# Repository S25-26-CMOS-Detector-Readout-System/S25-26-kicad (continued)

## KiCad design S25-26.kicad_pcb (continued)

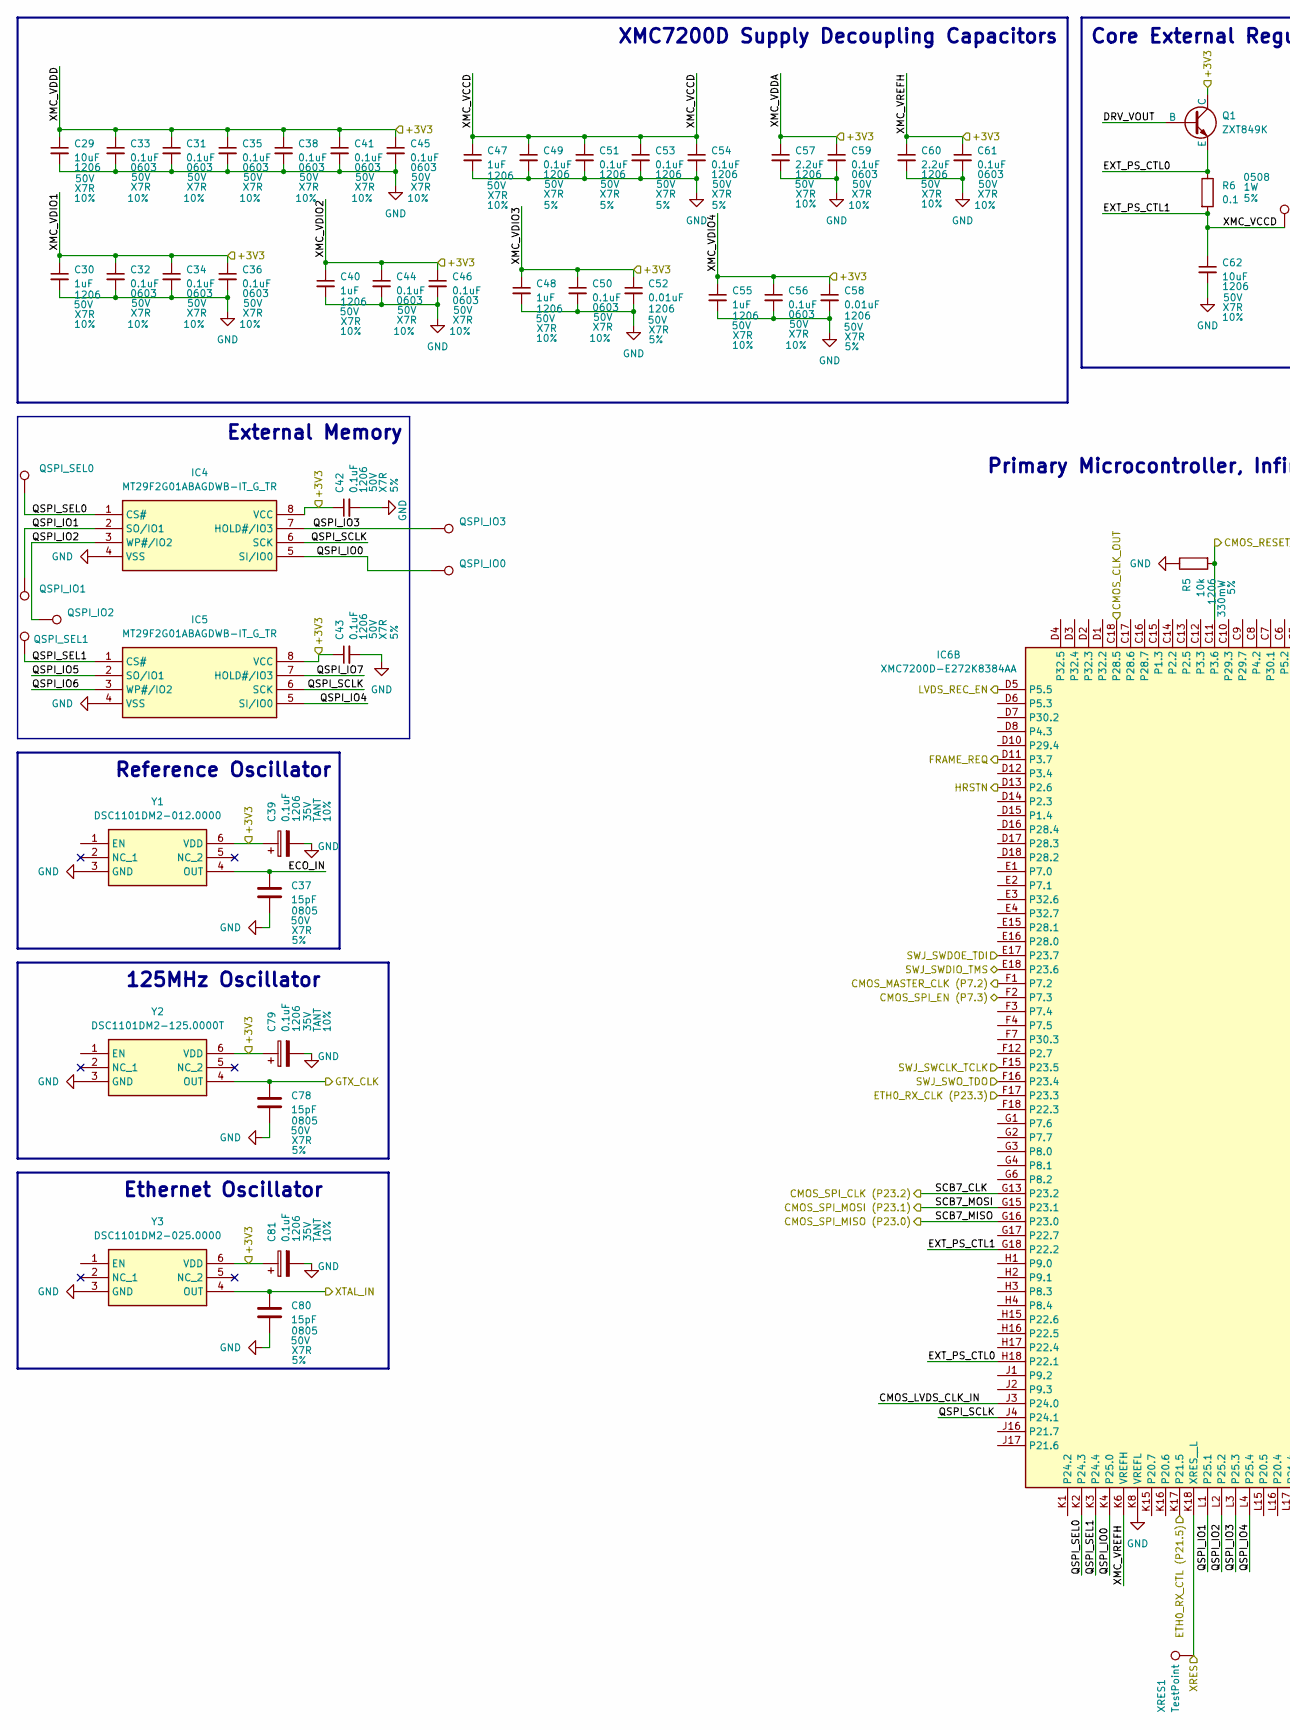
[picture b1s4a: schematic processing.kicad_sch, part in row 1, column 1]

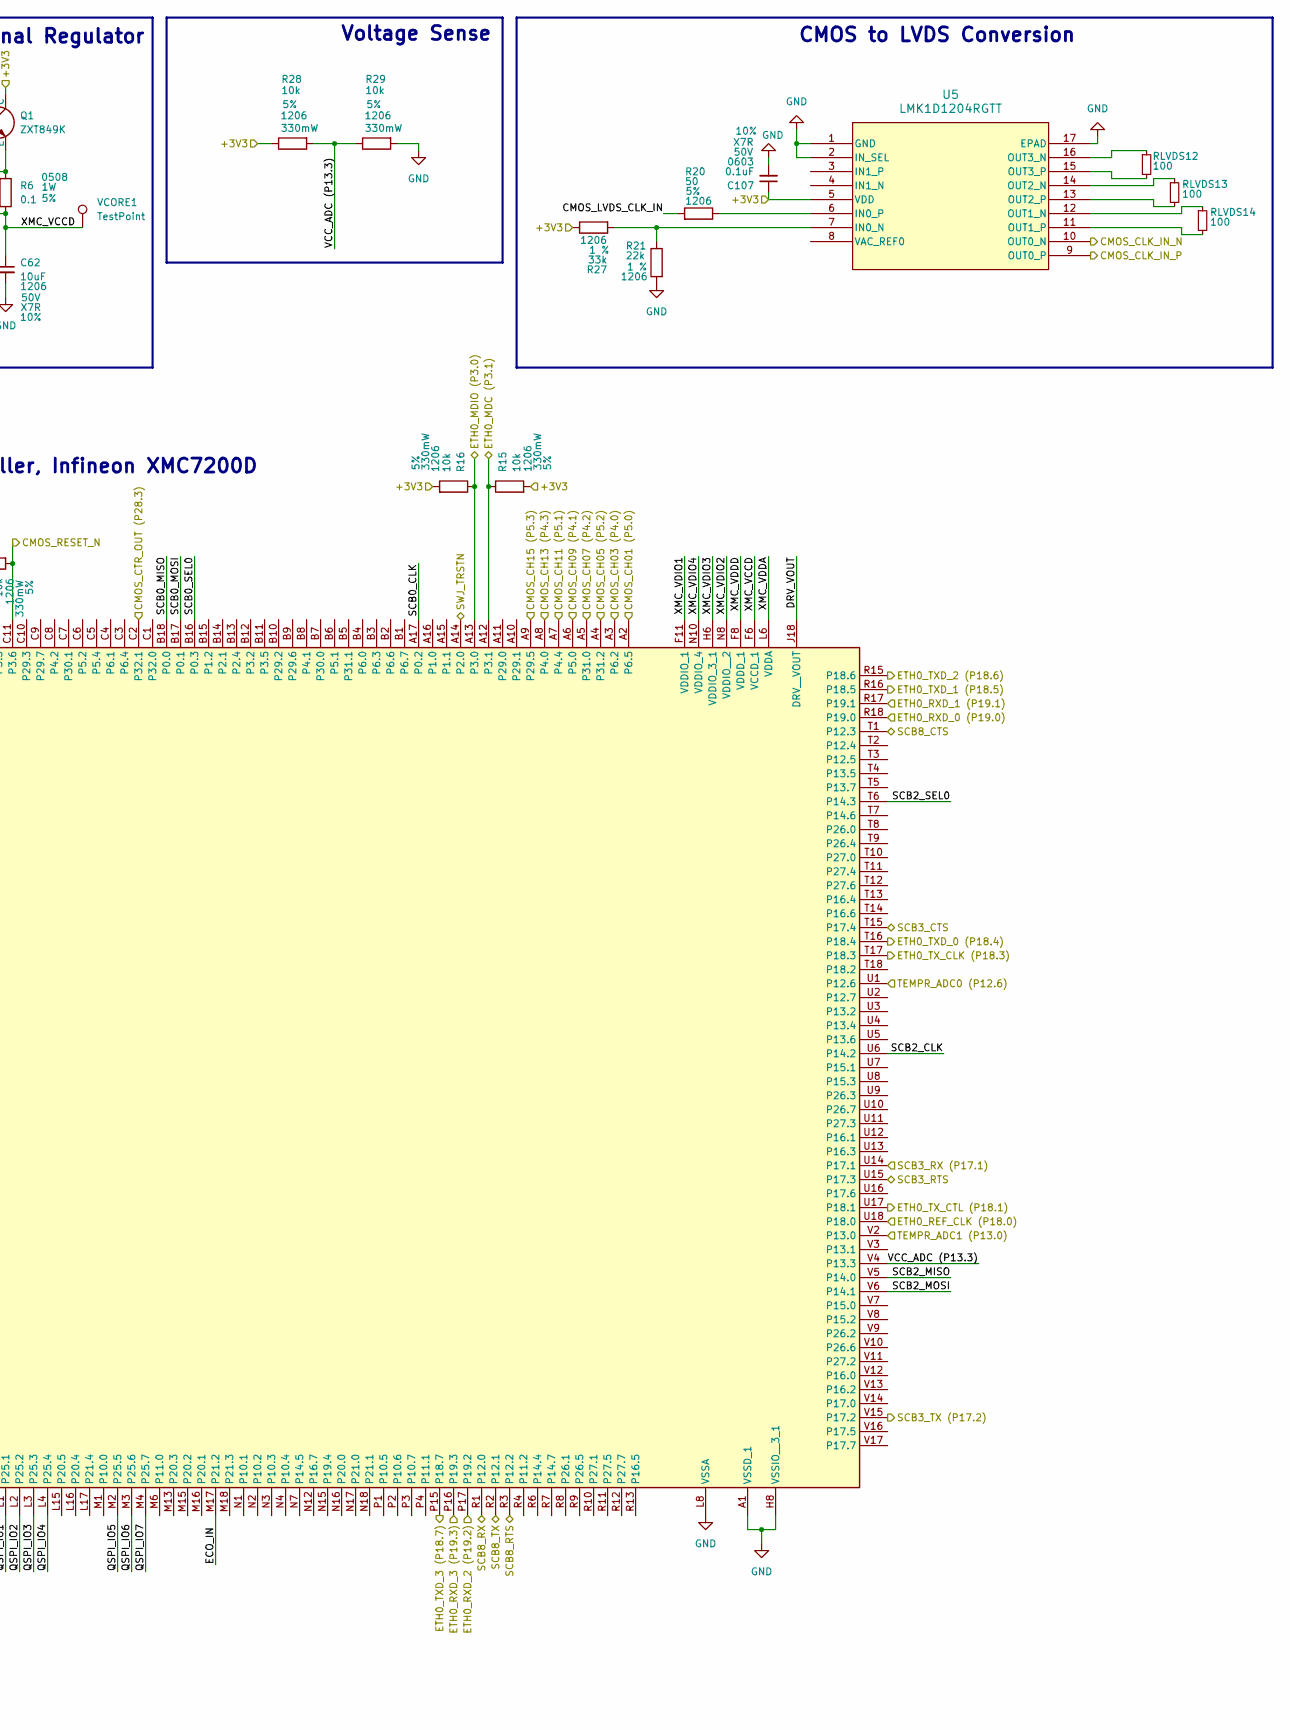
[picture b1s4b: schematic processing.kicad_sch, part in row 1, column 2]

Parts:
C29, C62: 10uF; C_1206_3216Metric; Voltage Rating 50V; Tolerance 10%; Mouser Part Number 187-CL31B106KBK6PJE
C30, C40, C47, C48, C55: 1uF; C_1206_3216Metric; Voltage Rating 50V; Tolerance 10%; Mouser Part Number 963-UMK316B7105KL-T
C31, C32, C33, C34, C35, C36, C38, C41, C44, C45, C46, C50, C56, C59, C61, C107: 0.1uF; C_0603_1608Metric; Voltage Rating 50V; Tolerance 10%; Mouser Part Number 963-UMK107B7104KAHT
C37, C78, C80: 15pF; C_0805_2012Metric; Voltage Rating 50V; Tolerance 5%; Mouser Part Number 80-C0805C150J5RACTU
C39, C79, C81: 0.1uF; C_1206_3216Metric; Voltage Rating 35V; Tolerance 10%; Mouser Part Number 581-TAJA104K035SNJ
C42, C43, C49, C51, C53, C54: 0.1uF; C_1206_3216Metric; Voltage Rating 50V; Tolerance 5%; Mouser Part Number 581-12065C104J4Z2A
C52, C58: 0.01uF; C_1206_3216Metric; Voltage Rating 50V; Tolerance 5%; Mouser Part Number 581-12065C103J4T4A
C57, C60: 2.2uF; C_1206_3216Metric; Voltage Rating 50V; Tolerance 10%; Mouser Part Number 80-C1206X225K5REAULR
IC4, IC5: MT29F2G01ABAGDWB-IT_G_TR; SON127P800X600X65-8N; Manufacturer_Part_Number MT29F2G01ABAGDWB-IT:G TR; Mouser Part Number 340-319922-REEL
IC6: XMC7200D-E272K8384AA; BGA272C80P18X18_1600X1600X170; Manufacturer_Part_Number XMC7200D-E272K8384AA; Mouser Part Number 726-C7200DE272K8384A
Q1: ZXT849K; TO-252-3_TabPin4; Mouser Part Number 522-ZXT849KTC
QSPI_IO0: QSPI_IO0; TestPoint_Pad_2.0x2.0mm
QSPI_IO1: QSPI_IO1; TestPoint_Pad_2.0x2.0mm
QSPI_IO2: QSPI_IO2; TestPoint_Pad_2.0x2.0mm
QSPI_IO3: QSPI_IO3; TestPoint_Pad_2.0x2.0mm
QSPI_SEL0: QSPI_SEL0; TestPoint_Pad_2.0x2.0mm
QSPI_SEL1: QSPI_SEL1; TestPoint_Pad_2.0x2.0mm
R5, R15, R16, R28, R29: 10k; R_1206_3216Metric; Power Rating 330mW; Tolerance 5%; Mouser Part Number 667-ERJ-T08J103V
R6: 0.1; R_1206_3216Metric; Power Rating 1W; Tolerance 5%; Mouser Part Number 755-LTR10LEZPJLR10
R20: 50; R_1206_3216Metric; Tolerance 5%
R21: 22k; R_1206_3216Metric; Tolerance 1 %
R27: 33k; R_1206_3216Metric; Tolerance 1 %
RLVDS12, RLVDS13, RLVDS14: 100; R_0603_1608Metric; Power Rating 0.2W; Tolerance 1%; Mouser Part Number 667-ERJ-P03F1000V
U5: LMK1D1204RGTT; VQFN16_RGT_TEX; Digikey Part Number 296-LMK1D1204RGTTCT-ND
VCORE1: TestPoint; TestPoint_Pad_D1.0mm
XRES1: TestPoint; TestPoint_Pad_D1.0mm
Y1: DSC1101DM2-012.0000; DSC1101DM20120000; Manufacturer_Part_Number DSC1101DM2-012.0000; Mouser Part Number 579-DSC1101DM2012
Y2: DSC1101DM2-125.0000T; DSC1101DM20120000; Manufacturer_Part_Number DSC1101DM2-125.0000T; Mouser Part Number 998-1101DM2125.0000T
Y3: DSC1101DM2-025.0000; DSC1101DM20120000; Manufacturer_Part_Number DSC1101DM2-025.0000; Mouser Part Number 998-1101DM2025.0000

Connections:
+3V3: C29.1, C30.1, C31.1, C32.1, C33.1, C34.1, C35.1, C36.1, C38.1, C39.1, C40.1, C41.1, C42.1, C43.1, C44.1, C45.1, C46.1, C48.1, C50.1, C52.1, C55.1, C56.1, C57.1, C58.1, C59.1, C60.1, C61.1, C79.1, C81.1, C107.1, IC4.8 (VCC), IC5.8 (VCC), IC6.F8 (VDDD_1), IC6.F9 (VDDIO__1_1), IC6.F10 (VDDIO__1_2), IC6.F11 (VDDIO_1), IC6.H6 (VDDIO_3_1), IC6.H13 (VDDD_2), IC6.J6 (VDDIO_3_2), IC6.J13 (VDDD_3), IC6.K6 (VREFH), IC6.K13 (VDDD_4), IC6.L6 (VDDA), IC6.L13 (VDDD_5), IC6.N8 (VDDIO__2), IC6.N9 (VDDIO__4), IC6.N10 (VDDIO_4), IC6.N11 (VDDD_6), Q1.1 (C), R15.2, R16.2, R27.1, R28.1, U5.5 (VDD), Y1.6 (VDD), Y2.6 (VDD), Y3.6 (VDD); also elsewhere on the board
/CMOS_CLK_IN_N: U5.10 (OUT0_N); also elsewhere on the board
/CMOS_CLK_IN_P: U5.9 (OUT0_P); also elsewhere on the board
/CMOS_MASTER_CLK: IC6.F1 (P7.2); also elsewhere on the board
/CMOS_RESET_N: IC6.C11 (P3.6), R5.2; also elsewhere on the board
/CMOS_SPI_CLK: IC6.G13 (P23.2); also elsewhere on the board
/CMOS_SPI_EN: IC6.F2 (P7.3); also elsewhere on the board
/CMOS_SPI_MISO: IC6.G16 (P23.0); also elsewhere on the board
/CMOS_SPI_MOSI: IC6.G15 (P23.1); also elsewhere on the board
/ETH0_MDC: IC6.A12 (P3.1), R15.1; also elsewhere on the board
/ETH0_MDIO: IC6.A13 (P3.0), R16.1; also elsewhere on the board
/ETH0_RXD_0: IC6.R18 (P19.0); also elsewhere on the board
/ETH0_RXD_1: IC6.R17 (P19.1); also elsewhere on the board
/ETH0_RXD_2: IC6.P17 (P19.2); also elsewhere on the board
/ETH0_RXD_3: IC6.P16 (P19.3); also elsewhere on the board
/ETH0_RX_CLK: IC6.F17 (P23.3); also elsewhere on the board
/ETH0_RX_CTL: IC6.K17 (P21.5); also elsewhere on the board
/ETH0_TXD_0: IC6.T16 (P18.4); also elsewhere on the board
/ETH0_TXD_1: IC6.R16 (P18.5); also elsewhere on the board
/ETH0_TXD_2: IC6.R15 (P18.6); also elsewhere on the board
/ETH0_TXD_3: IC6.P15 (P18.7); also elsewhere on the board
/ETH0_TX_CLK: IC6.T17 (P18.3); also elsewhere on the board
/ETH0_TX_CTL: IC6.U17 (P18.1); also elsewhere on the board
/FRAME_REQ: IC6.D11 (P3.7); also elsewhere on the board
/LVDS Conversion/CMOS_CH01: IC6.A2 (P6.5); also elsewhere on the board
/LVDS Conversion/CMOS_CH03: IC6.A3 (P6.2); also elsewhere on the board
/LVDS Conversion/CMOS_CH05: IC6.A4 (P31.2); also elsewhere on the board
/LVDS Conversion/CMOS_CH07: IC6.A5 (P31.0); also elsewhere on the board
/LVDS Conversion/CMOS_CH09: IC6.A6 (P5.0); also elsewhere on the board
/LVDS Conversion/CMOS_CH11: IC6.A7 (P4.4); also elsewhere on the board
/LVDS Conversion/CMOS_CH13: IC6.A8 (P4.0); also elsewhere on the board
/LVDS Conversion/CMOS_CH15: IC6.A9 (P29.5); also elsewhere on the board
/LVDS Conversion/CMOS_CLK_OUT: IC6.C18 (P28.5); also elsewhere on the board
/LVDS Conversion/CMOS_CTR_OUT: IC6.C2 (P32.1); also elsewhere on the board
/LVDS Conversion/LVDS_RECV_EN: IC6.D5 (P5.5); also elsewhere on the board
/Processing/CMOS_LVDS_CLK_IN: IC6.J3 (P24.0), R20.2
/Processing/DRV_VOUT: IC6.J18 (DRV__VOUT), Q1.2 (B)
/Processing/ECO_IN: C37.1, IC6.M17 (P21.2), Y1.4 (OUT)
/Processing/ETH0_REF_CLK (P18.0): C78.1, IC6.U18 (P18.0), Y2.4 (OUT); also elsewhere on the board
/Processing/EXT_PS_CTL0: IC6.H18 (P22.1), Q1.3 (E), R6.1
/Processing/EXT_PS_CTL1: C47.1, C49.1, C51.1, C53.1, C54.1, C62.1, IC6.F6 (VCCD_1), IC6.F13 (VCCD_2), IC6.G18 (P22.2), IC6.N6 (VCCD_3), IC6.N13 (VCCD_4), R6.2, VCORE1.1
/Processing/HRSTN: IC6.D13 (P2.6)
/Processing/QSPI_IO0: IC4.5 (SI/IO0), IC6.K4 (P25.0), QSPI_IO0.1
/Processing/QSPI_IO1: IC4.2 (SO/IO1), IC6.L1 (P25.1), QSPI_IO1.1
/Processing/QSPI_IO2: IC4.3 (WP#/IO2), IC6.L2 (P25.2), QSPI_IO2.1
/Processing/QSPI_IO3: IC4.7 (HOLD#/IO3), IC6.L3 (P25.3), QSPI_IO3.1
/Processing/QSPI_IO4: IC5.5 (SI/IO0), IC6.L4 (P25.4)
/Processing/QSPI_IO5: IC5.2 (SO/IO1), IC6.M2 (P25.5)
/Processing/QSPI_IO6: IC5.3 (WP#/IO2), IC6.M3 (P25.6)
/Processing/QSPI_IO7: IC5.7 (HOLD#/IO3), IC6.M4 (P25.7)
/Processing/QSPI_SCLK: IC4.6 (SCK), IC5.6 (SCK), IC6.J4 (P24.1)
/Processing/QSPI_SEL0: IC4.1 (CS#), IC6.K2 (P24.3), QSPI_SEL0.1
/Processing/QSPI_SEL1: IC5.1 (CS#), IC6.K3 (P24.4), QSPI_SEL1.1
/Processing/SCB0_CLK: IC6.A17 (P0.2)
/Processing/SCB0_MISO: IC6.B18 (P0.0)
/Processing/SCB0_MOSI: IC6.B17 (P0.1)
/Processing/SCB0_SEL0: IC6.B16 (P0.3)
/Processing/SCB2_CLK: IC6.U6 (P14.2)
/Processing/SCB2_MISO: IC6.V5 (P14.0)
/Processing/SCB2_MOSI: IC6.V6 (P14.1)
/Processing/SCB2_SEL0: IC6.T6 (P14.3)
/Processing/SCB3_CTS: IC6.T15 (P17.4); also elsewhere on the board
/Processing/SCB3_RTS: IC6.U15 (P17.3); also elsewhere on the board
/Processing/SCB3_RX (P17.1): IC6.U14 (P17.1); also elsewhere on the board
/Processing/SCB3_TX (P17.2): IC6.V15 (P17.2); also elsewhere on the board
/Processing/SCB8_CTS: IC6.T1 (P12.3); also elsewhere on the board
/Processing/SCB8_RTS: IC6.R3 (P12.2); also elsewhere on the board
/Processing/SCB8_RX: IC6.R1 (P12.0); also elsewhere on the board
/Processing/SCB8_TX: IC6.R2 (P12.1); also elsewhere on the board
/Processing/SWJ_SWCLK_TCLK: IC6.F15 (P23.5); also elsewhere on the board
/Processing/SWJ_SWDIO_TMS: IC6.E18 (P23.6); also elsewhere on the board
/Processing/SWJ_SWDOE_TDI: IC6.E17 (P23.7); also elsewhere on the board
/Processing/SWJ_SWO_TDO: IC6.F16 (P23.4); also elsewhere on the board
/Processing/SWJ_TRSTN: IC6.A14 (P2.0)
/Processing/TEMPR_ADC0 (P12.6): IC6.U1 (P12.6); also elsewhere on the board
/Processing/TEMPR_ADC1 (P13.0): IC6.V2 (P13.0); also elsewhere on the board
/Processing/VCC_ADC (P13.3): IC6.V4 (P13.3), R28.2, R29.1
/Processing/XRES: IC6.K18 (XRES__L), XRES1.1; also elsewhere on the board
/Processing/XTAL_IN: C80.1, Y3.4 (OUT); also elsewhere on the board
GND: C29.2, C30.2, C31.2, C32.2, C33.2, C34.2, C35.2, C36.2, C37.2, C38.2, C39.2, C40.2, C41.2, C42.2, C43.2, C44.2, C45.2, C46.2, C47.2, C48.2, C49.2, C50.2, C51.2, C52.2, C53.2, C54.2, C55.2, C56.2, C57.2, C58.2, C59.2, C60.2, C61.2, C62.2, C78.2, C79.2, C80.2, C81.2, C107.2, IC4.4 (VSS), IC5.4 (VSS), IC6.A1 (VSSD_1), IC6.A18 (VSSD_2), IC6.D9 (VSSD_3), IC6.G7 (VSSD_4), IC6.G12 (VSSD_5), IC6.H8 (VSSIO__3_1), IC6.H9 (VSSD_6), IC6.H10 (VSSD_7), IC6.H11 (VSSD_8), IC6.J8 (VSSIO__3_2), IC6.J9 (VSSD_9), IC6.J10 (VSSD_10), IC6.J11 (VSSD_11), IC6.J15 (VSSD_12), IC6.K8 (VREFL), IC6.K9 (VSSD_13), IC6.K10 (VSSD_14), IC6.K11 (VSSD_15), IC6.L8 (VSSA), IC6.L9 (VSSIO__4_1), IC6.L10 (VSSIO__4_2), IC6.L11 (VSSD__1), IC6.L18 (VSSD__2_1), IC6.M7 (VSSD_16), IC6.M12 (VSSD_17), IC6.P18 (VSSD__2_2), IC6.R5 (VSSD_18), IC6.R14 (VSSD_19), IC6.V1 (VSSD_20), IC6.V18 (VSSD_21), R5.1, R21.2, R29.2, U5.1 (GND), U5.2 (IN_SEL), U5.17 (EPAD), Y1.3 (GND), Y2.3 (GND), Y3.3 (GND); also elsewhere on the board
unnamed: R21.1, R27.2, U5.7 (IN0_N)
unnamed: R20.1, U5.6 (IN0_P)
unnamed: RLVDS14.1, U5.12 (OUT1_N)
unnamed: RLVDS14.2, U5.11 (OUT1_P)
unnamed: RLVDS13.1, U5.14 (OUT2_N)
unnamed: RLVDS13.2, U5.13 (OUT2_P)
unnamed: RLVDS12.1, U5.16 (OUT3_N)
unnamed: RLVDS12.2, U5.15 (OUT3_P)

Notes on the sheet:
Voltage Sense
Ethernet Oscillator
125MHz Oscillator
External Memory
Reference Oscillator
XMC7200D Supply Decoupling Capacitors
CMOS to LVDS Conversion
Primary Microcontroller, Infineon XMC7200D
Core External Regulator

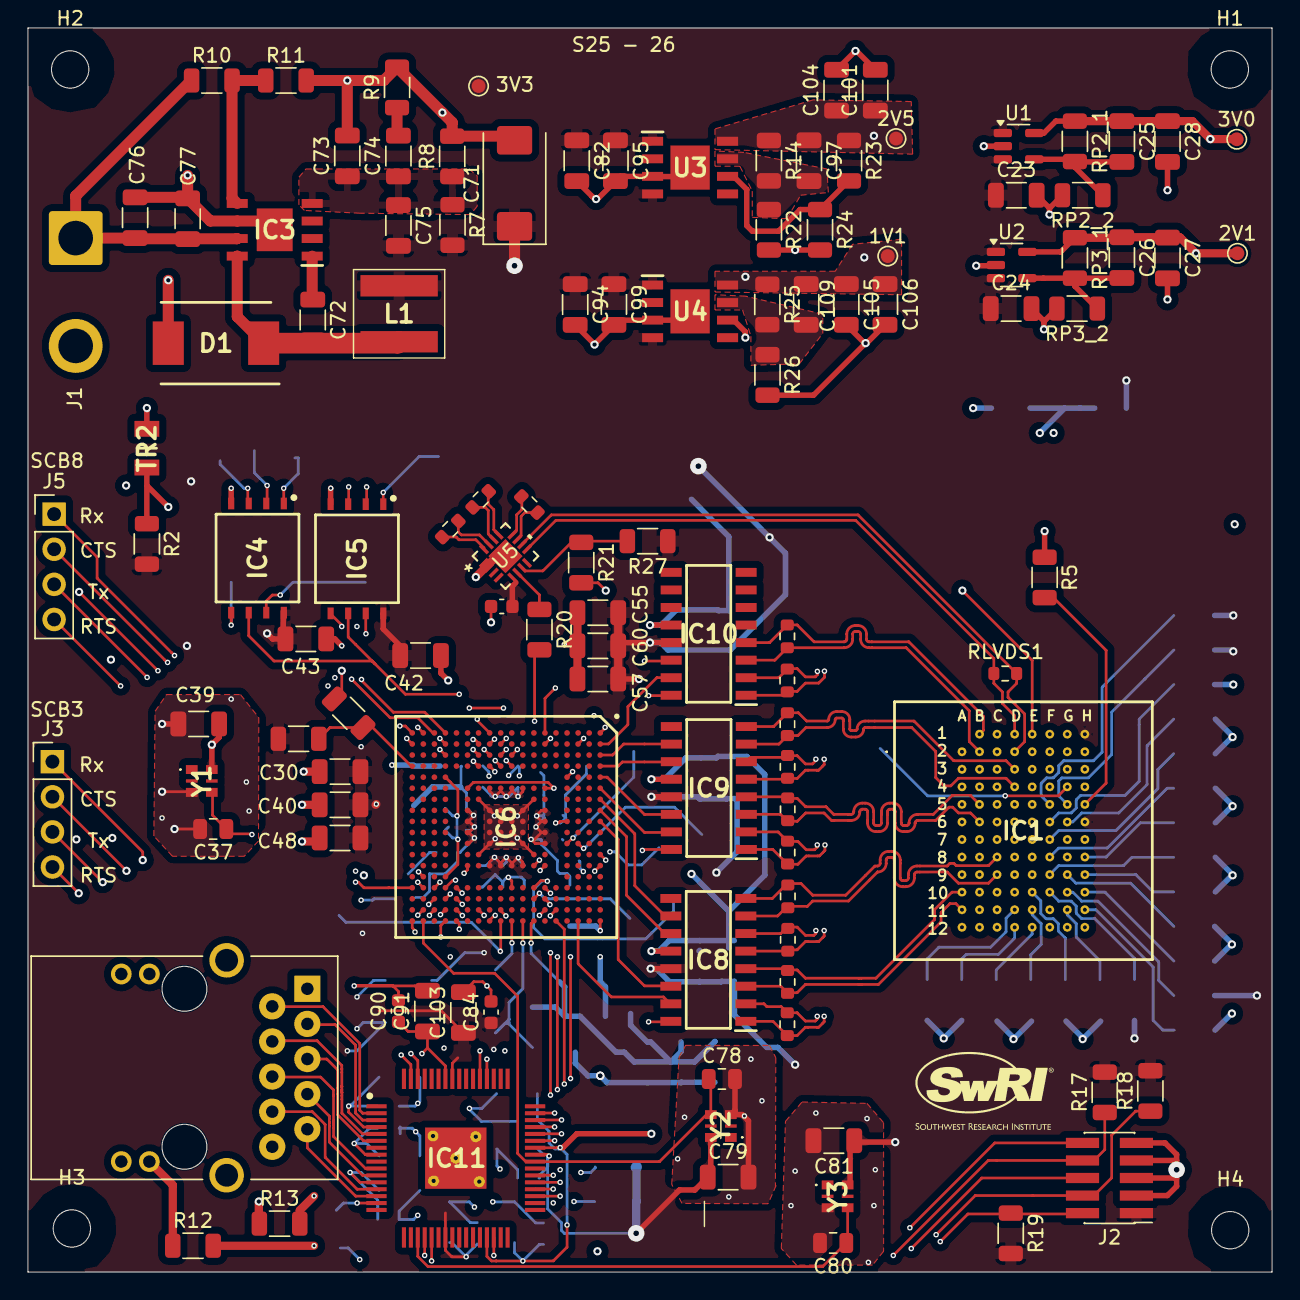
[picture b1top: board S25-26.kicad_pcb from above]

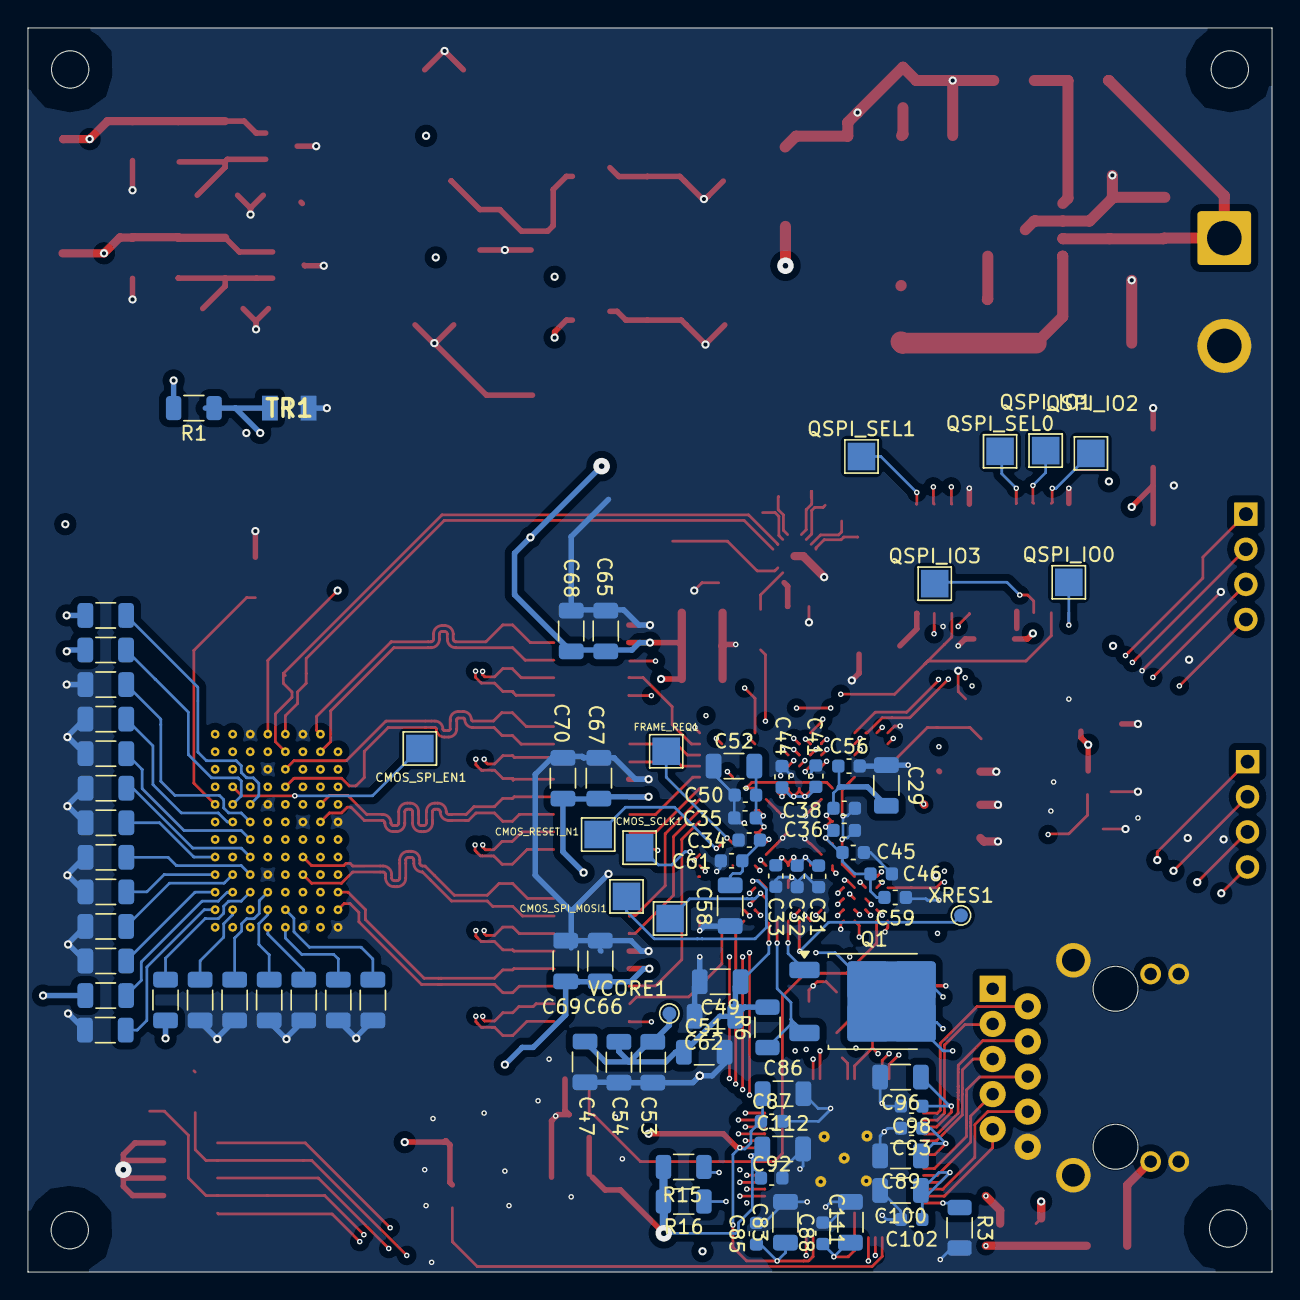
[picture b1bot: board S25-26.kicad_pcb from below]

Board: 6 copper layers, 90.0 x 90.0 mm, 202 parts (85 on the bottom side), 146 nets.

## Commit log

2024-11-13 Imported ICs
    Imported LVDS Receiver and Driver ICS and Voltage Regulator IC.
2024-11-15 First Draft
    Added Power Regulation, LVDS Serialization, and Processing sheets. Created schematics for voltage regulators and LVDS receivers, including inputs and outputs. Added symbols for all components. Added 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
2024-11-18 Ethernet Connections made; SPI connections made; TODO list in processing schem
2024-11-22 Corrected LVDS
2024-11-22 Processing Updates
    Added LVCMOS connections to MCU, added power regulation to MCU (NOT COMPLETE!)
2024-11-23 Added lots more connections
2024-12-03 Some Colors; GND net ties
2024-12-03 Condensed to one page schematic; added decoupling capacitors on MCU; added CLK connections, currently assuming any PWM pins can act as clkout, docs are rather vague; redid LVDS connections to represe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
2024-12-03 Add some preliminary pin connectors and RJ45; fix some ethernet phy connections
2024-12-23 Voltage Regulator Minor Edits
    Changed how the I/Os of the voltage regulation systems look, using the specific input and output labels.
2024-12-23 Voltage Input Symbols Edited
    Changed into global input/output symbols for easier readability
2025-01-24 Implementing Global Labels
    Swapping generic I/O labels for global labels to help provide clarity in the schematic. Completed Supply Decoupling Caps, Temp. Sensing, Voltage Regulation, and part of Core Ext. Regulator
2025-02-05 Reverted schematic to hierarchical structure.
    The following connections are known to be floating:
    FRAME_REQ
    CMOS_RESET_N
    CMOS_CLK_OUT
    ETH0_RX_ER
    ETH0_ETH_TSU_TIMER_CMP_VAL
2025-02-05 Auto Generated PCB
    Autogenerated PCB and found substitute footprint for the linear voltage regulator
2025-02-05 Some small revisions
2025-02-05 One gnd to rule them all; PCB border (90 mm x 90 mm)
2025-02-05 3v3 Regulator routed; zones for 3v3 and gnd
2025-02-07 Schematic - Component Specifics
    Fixed floating connections.
    Added parameters, footprints, Mouser part numbers, and Mouser links to all symbols, including discrete components and ICs.
    The following symbols do not have Mouser part numbers or Mouser links:
    CMOS Sensor (not required)
    RJ45 Connector
    JTAG Connector
2025-02-12 QSPI Lines for 100 MHz channel
2025-02-12 Some small changes for BOM
2025-02-15 Ethernet Transceiver
2025-02-17 Memory layout completed
2025-02-21 Lots of PCB changes, some small parts changes
    Updated parts footprints from those found in MDE Lab. Some parameters may be incorrect, but all footprints should be correct
    Drew most of PCB. CMOS SPI still needs connection. Decoupling caps on MCU still need connection. Power and ground needs to be analyzed, and some components may not have power or ground connected.
2025-02-24 Adjusted board setup for AdvancedPCB; fixed many DRC errors
2025-02-24 Fixed DRC; all connections made
2025-02-26 Testpads everywhere; passives' footprints updated from MDE components; bigger DC_IN pads
2025-02-27 move toplevel to accomadate test pads
2025-02-28 Final Changes before Order
2025-03-05 Watch Out: David's Mounting Holes
2025-03-25 Lots of small changes
    Some power and ground planes need to be looked at
    All parts need to be reexamined before ordering
2025-03-25 See previous push
2025-03-26 Added text to pinheaders for JTAG and UART
2025-03-27 Almost done
    Taking a break and making a push. Known things to do:
    Add pull-up resistors to ETH MDIO, ETH MDC, and XRESL.
    Source a 100uF capacitor for primary regulator.
2025-03-28 Ready to order
    Still unsure about 100uF cap
2025-03-28 Labeled test pads; marked tantalums with lines for cathode; found suitable tantalum for 100 uF
2025-03-28 S25 - 26 Text Added
2025-03-29 Some teeny changes
2025-04-02 CMOS Sensor Grid Text
2025-04-18 Beginning of V3
    Long way to go
2025-04-19 Excluded TPs from BOM
2025-04-22 V3 Overhaul
    Things remaining:
    Ethernet Transceiver Clocks
    Output Filtering on DC-DC Converter
    Update some part numbers
2025-04-22 Some mild V3 changes
2025-04-24 V3 Almost Final
    Move LVDS driver/change part if decided
    Add thermal vias to GND pads of LDOs and ETH PHY.
2025-04-30 Keepouts on mounting holes, QSPI on different lines, new LVDS clock buffer, voltage sense circuit
